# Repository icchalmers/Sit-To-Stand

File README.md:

# Sit-To-Stand Stroke Rehabilitation

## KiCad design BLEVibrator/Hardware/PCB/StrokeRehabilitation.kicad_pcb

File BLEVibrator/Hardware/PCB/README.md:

# BLE Vibrator: PCB

The PCB was designed in KiCAD, with the intention of using cheap 2-layer fab houses. Specifically, the board was designed with [OSH Park's design rules](http://docs.oshpark.com/design-tools/kicad/kicad-design-rules/).

# BOM 

The parts in the schematic all include a manufacturer’s part number for the exact component I have used. Many of the parts will work just fine with an equivalent e.g. a different brand of resister, a specification equivalent MOSFET etc.

I used [KiCost](https://github.com/xesscorp/KiCost) to generate a rough costing for the components. See [StrokeRehabilitation_KiCost.xlsx](./StrokeRehabilitation_KiCost.xlsx). Note that this is based on US price, and does not include the vibration motor or the LiPo battery. Note that a working unit also needs a case and some way of attaching it to the user - these costs are also not included.

Most of the passives are 0805, with the exception of the LiPo voltage measuring circuitry. The two resistors and one capacitor are 0603. This is purely based on the components I could source quickly and to let me try 0603 as a size.

# Improvements

There are two minor issues with the current PCB design. 

* The footprint for soldering the motor wires is fiddly. A single hole with a long strip to solder the wire to would probably be just as secure and save a lot of assembly hassle.
* The holes for soldering the battery wires are a __nightmare__. The wires are not very flexible so if they length is even slightly off it makes getting the whole assembly together a frustrating experience. I got rid of the JST connector because it was the tallest component and took up a lot of room. In any future design I would leave a lot more space (probably in the case) for wire management or find a lower profile connector to use instead.

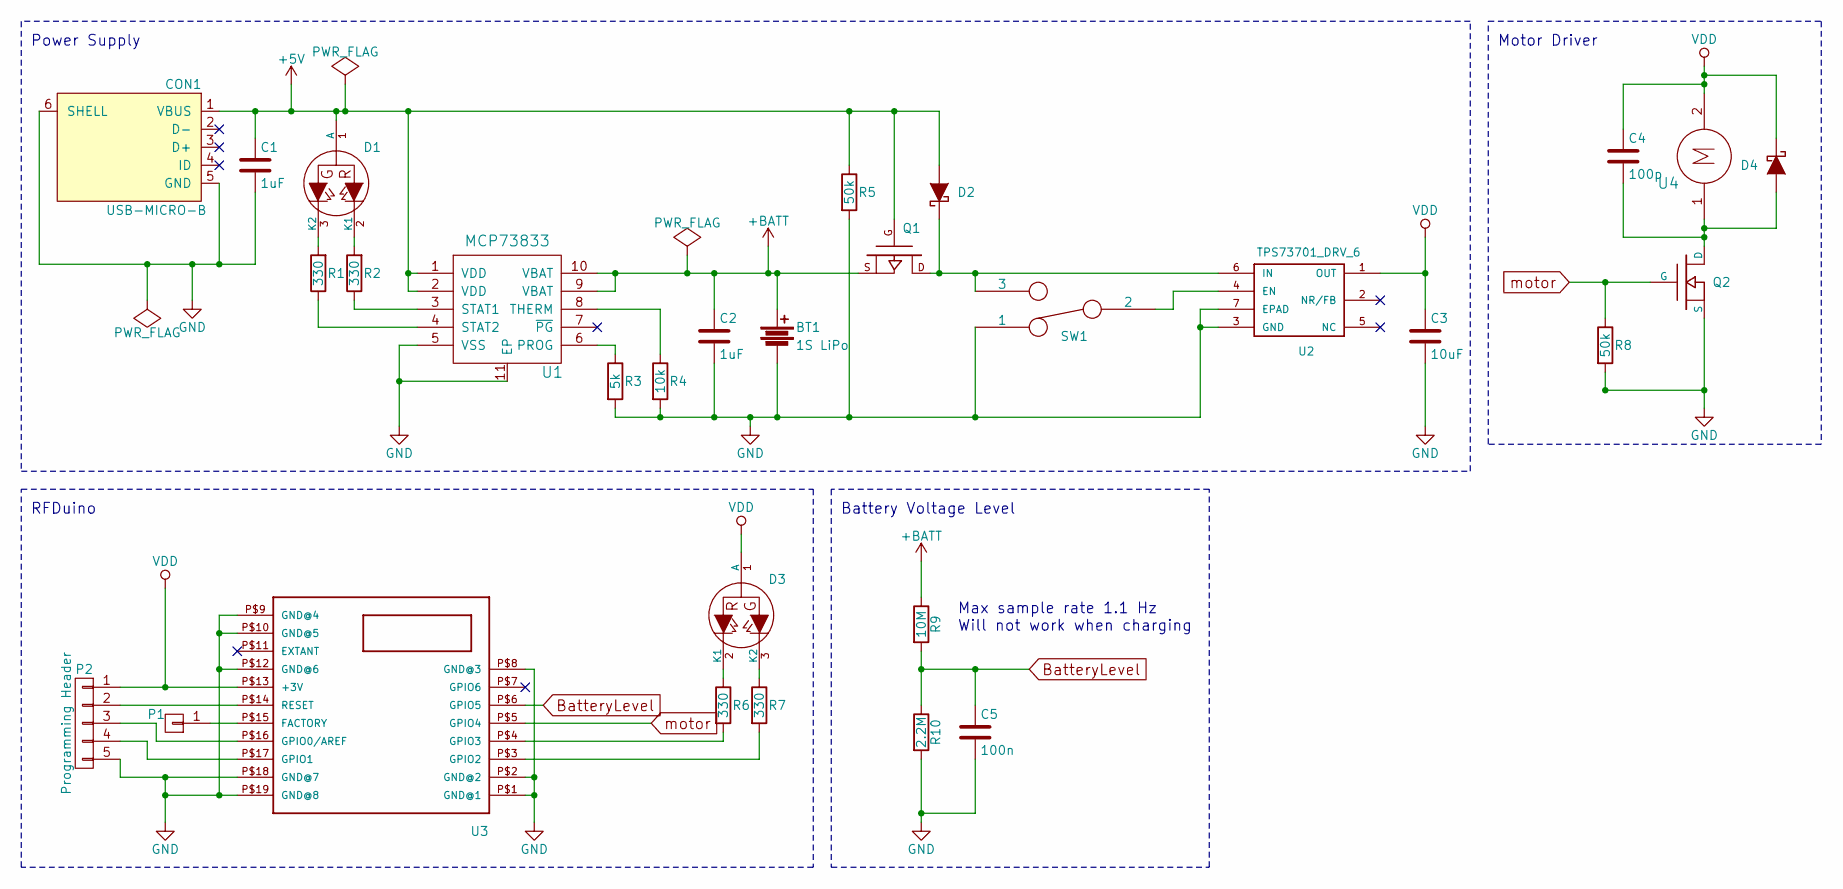
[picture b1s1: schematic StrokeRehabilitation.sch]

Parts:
BT1: 1S LiPo; BatteryCon_WireSolder_0.8mm
C1, C2: 1uF; Murata_capacitor_SMD_0805_reflow
C3: 10uF; Murata_capacitor_SMD_0805_reflow
C4: 100p; Murata_capacitor_SMD_0805_reflow
C5: 100n; C_0603
CON1: USB-MICRO-B; Micro_USB_Amphenol_10118192-0001LF
D1, D3: BI_LED_common_anode; Bi_LED_SM1204BC-RG
D2, D4: D_Schottky; SOD-123F
P1: CONN_01X01; TestPoint_SMD_1x1
P2: Programming Header; RFDuino_programming_header
Q1: MOS_P; Vishay_SOT-23
Q2: MOSFET_N; MCPH3_SOT-323
R1, R2, R6, R7: 330; Yageo_resistor_SMD_0805_reflow
R3: 5k; Yageo_resistor_SMD_0805_reflow
R4: 10k; Yageo_resistor_SMD_0805_reflow
R5, R8: 50k; Yageo_resistor_SMD_0805_reflow
R9: 10M; R_0603
R10: 2.2M; R_0603
SW1: SWITCH_INV; SlideSwitch_SSSS810701
U1: MCP73833; MCP73833-XXX_MF
U2: TPS73701_DRV_6
U3: RFD22301; RFD22301_RFDuino
U4: Brushed_DC_motor; WireToBoard_1x2_TensionRelief

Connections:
+5V: C1.1, CON1.1 (VBUS), D1.1 (A), D2.2 (A), Q1.G, R5.1, U1.1 (VDD), U1.2 (VDD)
+BATT: BT1.1, C2.1, Q1.S, R9.1, U1.9 (VBAT), U1.10 (VBAT)
BatteryLevel: C5.1, R9.2, R10.1, U3.P$6 (GPIO5)
GND: BT1.2, C1.2, C2.2, C3.2, C5.2, CON1.5 (GND), CON1.6 (SHELL), P2.5, Q2.S, R3.2, R4.2, R5.2, R8.2, R10.2, SW1.1, U1.5 (VSS), U1.11 (EP), U2.3 (GND), U2.7 (EPAD), U3.P$1 (GND@1), U3.P$2 (GND@2), U3.P$8 (GND@3), U3.P$9 (GND@4), U3.P$10 (GND@5), U3.P$12 (GND@6), U3.P$18 (GND@7), U3.P$19 (GND@8)
unnamed: C4.2, D4.2 (A), Q2.D, U4.1
unnamed: D1.2 (K1), R2.2
unnamed: D1.3 (K2), R1.2
unnamed: D2.1 (K), Q1.D, SW1.3, U2.6 (IN)
unnamed: D3.2 (K1), R6.1
unnamed: D3.3 (K2), R7.1
unnamed: P1.1, U3.P$15 (FACTORY)
unnamed: P2.2, U3.P$14 (RESET)
unnamed: P2.3, U3.P$16 (GPIO0/AREF)
unnamed: P2.4, U3.P$17 (GPIO1)
unnamed: R1.1, U1.4 (STAT2)
unnamed: R2.1, U1.3 (STAT1)
unnamed: R3.1, U1.6 (PROG)
unnamed: R4.1, U1.8 (THERM)
unnamed: R6.2, U3.P$4 (GPIO3)
unnamed: R7.2, U3.P$3 (GPIO2)
unnamed: SW1.2, U2.4 (EN)
VDD: C3.1, C4.1, D3.1 (A), D4.1 (K), P2.1, U2.1 (OUT), U3.P$13 (+3V), U4.2
motor: Q2.G, R8.1, U3.P$5 (GPIO4)

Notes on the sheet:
Power Supply
RFDuino
Motor Driver
Max sample rate 1.1 Hz Will not work when charging
Battery Voltage Level

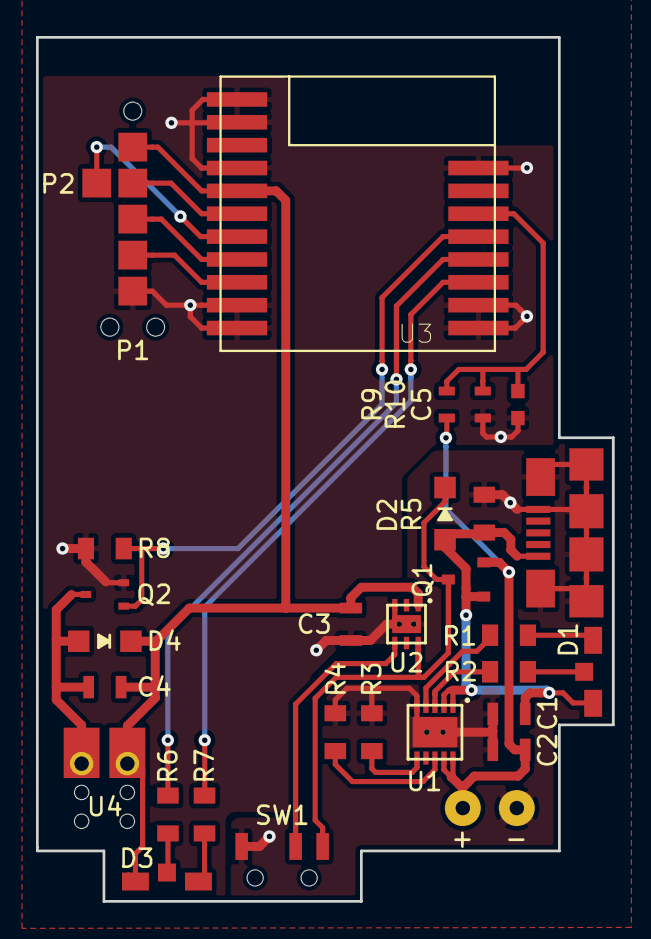
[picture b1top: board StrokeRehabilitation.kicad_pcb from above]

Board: 2 copper layers, 32.0 x 48.0 mm, 30 parts (0 on the bottom side), 23 nets.

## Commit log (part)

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2015-01-30 Initial Application uploaded to BitBucket, currently reads Gyroscope values and displays them on the screen
2015-02-02 Moved JavaScript code for motion to external JavaScript file
2015-02-03 Set up JS to read values of motion 10 times a second, and display the average of each 0.5 second on screen
2015-02-03 Updated motion.js to run faster
2015-02-05 Updated text to show only the motion acceleration field, with large size text
2015-02-05 Created Android application to house the webView to run HTML code from
2015-02-06 Added URL of devweb site to Android application to load correct application on start up.
2015-02-11 Moved code from current project onto devweb, and setup new project for editing this
2015-02-11 Changed code to focus on orienation values, and set time to average and update displayed values
2015-02-13 Added bootstrap framework to improve UI
2015-02-17 Synchronised with devweb
2015-02-18 Added some comments to make it more readable
2015-02-18 Added setup script to get screen dimensions and create button to start program
2015-02-19 Added AngularJS locally to enable faster loading times Set-up start button to disappear when clicked and calibration page to appear Started calibration page Added Progress bar to calibration page
2015-02-19 Fixed issue of progress bar always being visible even when not active
2015-02-23 Updated HTML, removing unused code
2015-02-24 Added sounds and failed to implement them
2015-03-02 Sound finally works!
2015-03-03 Removed unused methods and variables
2015-03-03 Updated switching screens to give strings rather than ints to make understanding current screen easier Removed AngularJS docs to make app smaller Fixed OrientationEvent to only take one reading at a 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
2015-03-04 Implemented calibration fully Implemented next screen to show raw data, calibrated values and differentials Added button for done to restart program
2015-03-04 Removed documentation for AngularJS Added smoothing to alpha to help with jumpy results Added reset button to restart application when completed
2015-03-05 Linked Javascript to Android and enabled passing a message to be displayed as Toast on phone
2015-03-06 Utilised link between JS and Android to write messages to file Setup code to write values to a message to be stored Stored all raw values and averaged values to text file
2015-03-09 Increased font sizes to make reading easier when recording user tests Added smoothing algorithm to beta and gamma Normalised alpha to run from 0 to 360 Changed calibration time to 15s
2015-03-12 Removed sampling rate to record all orientation events Averaging over 0.5s - provides much smoother results although slight lag Fixed JSLint errors Removed unused script files
2015-03-12 Removed unused AngularJS files
2015-03-13 Added check for Android to stop crash on other OS
2015-03-17 Added start screen that allows BT connection
2015-03-17 Made buttons larger on first screen Doubled values of gamma so it now displays in 360 degree
2015-03-18 App now changes background colour dependant on how far user is from centre. Intensity increases as user moves further from centre
2015-03-19 Added Arduino code to repository Simple code to test communication between Arduinos to find working Xbee modules
2015-03-19 Updated code to allow multiple bytes to be sent and read
2015-03-19 Code now recieves serial by bluetooth and sends it on to the other Arduino
2015-03-19 Configured webApp to send messages to Arduino Setup High/Low buttons to toggle light on Arduino for testing Removed unused classes in Android
2015-03-23 Updated Arduino code to enable/disable vibration when high and low is pressed on the JS app
2015-03-23 Made some nice CSS for full-screen and centre-vertical to replace horrible JS method for full screen button, should be more universal
2015-03-24 JS now tells motors to vibrate when angle is more than 30 degree from calibrated. Currently both motors vibrate at the same time
2015-03-24 Changed averaging rate to 10Hz
2015-03-24 Updated codes to set one motor on when left and the other when right
2015-03-24 Fixed error that stopped arduino from clearing message. Message was constantly being expanded in JS, added clear method that should solve issue.
2015-03-26 Fixed issue where sending HIGH to Arduino after using it once would not set correct speed
2015-03-26 Fixed issue where beta angle flipped when gamma flipped by manipulating angle if gamma flips Moved code to ignore first value after gamma flips Refactored HTML to move all areas into individual divs,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
2015-03-30 Removed unused code snippets Fixed JSLint complaints
2015-04-09 Minor tweaks to improve stability
2015-04-22 Cleaned up code
2016-03-03 Replace original Arduino code with RFDuino code to match the new vibration hardware
2016-03-03 Fixing top level naming structure
2016-03-03 Changed module name to use a numeric identifier
2016-03-03 Adding usage description to RFDuino sketch
2016-03-04 Created new blank Android Studio project, ready to port old Eclipse project source into
2016-03-04 Adding git integration to Android Studio project
2016-03-04 Update launcher icon
2016-03-04 Moved HTML assests
2016-03-04 moving layout and java code
2016-03-04 Remove the leftover old Android project files - they were almost exclusively generated and didn't need source controlled anyway
2016-03-04 Adding BluetoothLeService class from Android BLE example
2016-03-23 Adding blank activities for scanning and controling motors
2016-03-23 adding map of RFDUino service and characteristic UUIDs
2016-03-23 Adding simplified GattManager, based on the code from https://github.com/NordicSemiconductor/puck-central-android/tree/master/PuckCentral/app/src/main/java/no/nordicsemi/puckcentral/bluetooth/gatt
2016-03-23 Adding Droidparts dependency to gradle build
2016-03-23 Adding basic menus
2016-03-23 Didn't actually need these...
2016-03-23 Adding new layout commponents
2016-03-23 Fix a typo
2016-03-23 First attempt at getting BLE integrated. Still lots of bugs...
2016-03-23 update manifest to start app with a scan activity
2016-03-23 opening to a debug page by default
2016-03-23 Updating styles
2016-03-23 General project files update
2016-03-25 Request lcoation permission to get around bug in Android M where scan results are otherwise missing. General clean up of BLE management code. Can now reliably write to two BLE devices at the same tim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
2016-03-28 Getting ready to integrate BLE comms with original HTML5 code
2016-03-28 Forgot to take in the View. Also minor cleanup oof potential null pointer exception on action bar
2016-03-28 Adding null check on scanner object. Need a cleaner way of ensuring bluetooth is enabled but this will do for now...
2016-03-28 Moving variable declaration to top
2016-03-28 Making motor controls disabled until the connections have been made
2016-03-28 renaming BluetoothLEService to BLEMotorService
2016-03-28 Adding funtionality to Calibrate button. The HTML based part of the app can now connect and send to the motors
2016-03-28 Working! Shifts on the angle of the phone now get sent as feedback to the motors. Currently only works when phone is in the original landscape orientation
2016-03-28 Addind a scaling factor to the vibration feedback to better match angle offset from stright
2016-03-28 Forcing app to always be in portrait mode
2016-03-28 Change loging tag for messages from the HTML
2016-03-28 Fix bug in angle calibration
2016-03-28 Added some crude low pass filtering on orientation angle data to help remove noise. Alpha is still quite susceptible to large variations due to it using the magnetic compass which is pretty unstable
2016-03-28 Adding TODO for coordinate translation from Earth to Device
2016-03-29 Stopped BLEMotorService leaking from screen activity on back buttoning
2016-03-29 Fixing action bar to display buttons
2016-03-29 Code cleanup
2016-03-29 Changing title of MotorControlActivity
2016-04-04 Using DeviceMotion events to calculate the users lean based on accelerometer gravity readings
2016-04-04 Adding functionality to get the device yaw using the Android SensorManager. Using the JS deviceMotion and deviceOrientation events in JS was very device dependent. This way, it should be a bit more m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
2016-04-04 Updating to use Android SensorManager based calculated 'yaw' rather than azimuth (the degrees to north. This is done using a quick-fix of just grabbing the SensorManager based yaw when deviceOrientat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
2016-04-05 Adding some crude disconnect functionality to the motor setup activity (MotorControlActivity). There are some bad interactions when a user start calibration and then uses the back button.
2016-04-05 Updated MotorControlACtivity to have more useful features. Removed the 'Disable Motors' button and the slider. Instead, replaced with buttons that trigger a 1s pulse on the left/right motors and also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
2016-04-05 Fixed app icon label
2016-04-05 Adding the 3d printed case design files
2016-04-05 Initial commit of PCB files
2016-04-05 Merging BLE branch.
    The project now has completely redesigned vibration motors designed around Bluetooth Low Energy connections. The app has been updated accordingly.
2016-04-05 Removing old redundant files
2016-04-05 Adding CC Attribution-NonCommercial-ShareAlike 4.0 International licence
2016-04-05 Fixing license header on files that came from example code that had an exising licence
2016-04-05 General code cleanup and some extra comments
2016-04-05 Abstracting out some common code for motor identification
2016-04-05 Moved variables that govern the app operation to be more obvious and accessible at the top of the file
2016-04-25 Adding hardware overview readme
2016-04-25 Fix typo
2016-04-25 Fix another typo...
2016-05-22 Making the deadzone/bandwidth a user controllable parameter
2016-06-06 Updated the PCB to have a side-mounted slide switch and connection status LED. The case still needs to be updated to match
2016-06-06 adding .gitignore for KiCad backup files
2016-06-06 Adding Inventor project file
2016-06-06 Updating case to have a slot for the new side mounted switch and LED. Also made battery slot 1mm longer to match the batch of 440mAh batteries I get sent that are slightly longer than the 400mAh. Als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
2016-06-06 Updating the Makerbot file to use the new STLs
2016-06-06 Typo
2016-06-09 Increased the width of the slot on the front of the case for the switch/LED to make it a slightly less snugg fit
2016-06-13 reduced size of extension for 440mAh battery slot from 1mm to 0.5mm based on printed prototype
2016-06-13 Moved side mount LED back a little bit to make placement and soldering easier
2016-06-20 Adding KiCAD autosave files to .gitignore
2016-06-20 Cleaned up schematic. Fixed symbols to have pins for matching footprints e.g. exposed thermal pads. Changed LED resistors from 500 to 330 (closer to 4 mA per pin limit of RFDuino, and still within 20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
2016-06-22 Routed the new PCB. Assigned correct footprints in schematic
2016-06-24 Added circuitry to enable monitoring of the LiPo voltage. Based on https://devzone.nordicsemi.com/question/990/how-to-measure-lithium-battery-voltage/ and https://devzone.nordicsemi.com/blogs/30/meas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
2016-06-24 Place and route of LiPo voltage monitoring circuit
2016-06-24 Adding a test point for FACTORY pin of the RFDuino, in case SWD programming is needed in the future
2016-06-24 Added back silkscreen with board info
2016-06-24 New gerbers generated for v0.3 i.e. the first iteration of the board to be double sided and professionally fabricated
2016-06-24 Added manufacturer part numbers to parts in schematic. Generated a BOM in KiCAD and a rough costing (US-based) using KiCost
2016-06-24 adding formatting to comment
2016-06-24 Fixing link formatting
2016-06-24 Fixing link formatting - I'm really bad for mixing my brakets apparently...
2016-06-24 Cleaned up silkscreen label placement
2016-08-01 Marking Inventor assembly .iam, Inventor part .ipt, .STL and .thing files as binary
2016-08-01 New case to fit the new motor and the new PCB
2016-08-01 Update README with info on velcro strap
2016-08-01 Update readme for PCB
